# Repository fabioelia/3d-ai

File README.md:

# Caliper

A browser CAD tool for 3D-printable parts, in the spirit of Fusion's sketch → extrude → fillet workflow but with far fewer knobs. Bring the AI you already use (Claude Code, Codex, Cursor, Claude or ChatGPT in the browser) through [AI Connect](https://github.com/fabioelia/ai-connect): it sees, measures and edits the same model you are looking at, while you watch. Caliper calls no model and needs no API key.

**Live:** https://fabioelia.github.io/3d-ai/

- **Real solid modelling.** The geometry kernel is OpenCascade compiled to WebAssembly (through [replicad](https://replicad.xyz)), running in a worker. Fillets, chamfers, shells and booleans are exact B-rep operations, not mesh tricks, and STEP export keeps them exact.
- **Parametric timeline.** Every feature stays editable. Any number can be an expression over named parameters (`width/2 - wall`), and the model rebuilds as you type.
- **Sketching without constraints.** Rectangles, circles, polygons, slots, line paths and text snap to a grid and to each other; exact sizes go in the inspector. A shape drawn inside another becomes a cut-out.
- **Direct manipulation.** Click a face to sketch on it or push/pull it; click edges to fillet or chamfer them; click a face and Shell to hollow the part.
- **Your own AI, through AI Connect.** Your AI gets the whole app as tools: the full state, screenshots of what you see, exact geometry and measurements, printability checks, every edit, your selection, your camera, import and export. See [Use it with your own AI](#use-it-with-your-own-ai-ai-connect).
- **Chat in Caliper.** Type in the side panel; your connected AI listens there, works on the model with the same tools and answers in the panel. Drop, paste or attach images (photos, sketches), 3D files and documents (notes, CSV, schematics such as Eagle `.sch`): text goes with your message, your AI looks at images with the `get_attachments` tool, and 3D files go into the model.
- **3D import.** STL, STEP/STP, OBJ and 3MF, or the zip a model site or a colleague sent. STEP with real surfaces comes in as exact solids; meshes (including Fusion's mesh-only "tessellated" STEP) are repaired automatically (zero-area slivers, T-junctions, duplicate faces, near-miss vertices). Small clean meshes become exact solids whose flat faces you can sketch on, fillet and shell; larger ones become mesh bodies you can move, cut, join and pattern; files that still are not closed solids come in as reference meshes you can view, move, measure and export. Other files in a zip go to the chat when you drop it there.
- **Circuit boards.** Like the board editors in Fusion, Eagle or KiCad. Import an Eagle / Fusion Electronics schematic (`.sch`) or board (`.brd`), or a KiCad board (`.kicad_pcb`), schematic (`.kicad_sch`) or netlist (`.net`): every part comes in with its footprint, pads, body size and height, plus the nets (KiCad schematics and netlists get footprints from KiCad's standard footprint names), and board files also bring their outline, holes, placement and copper. Place parts in a top-down editor (drag, turn with R, flip to the bottom with F, nudge, holes, outline, automatic arrangement on one or both sides) with airwires and live clash checks. Arrange parts automatically with connected parts kept together, or tidy your own layout for shorter connections. Fit the outline to the inside of your enclosure. Route on two copper layers by hand (45° traces, vias) or with the autorouter, add a ground pour (with thermal reliefs for hand soldering), with design-rule checks (clearance, shorts, edge and hole clearance, widths, drills) as you go. Parts are drawn as real-looking 3D models by kind (banded resistors on bent leads, capacitors, headers with pins, modules on their pins, chips), or use your own STEP/STL per part; copper shows in 3D too. Model the enclosure around the board, check the fit, and add printed standoffs with screw pilot holes under the board's mounting holes. Read part heights from a sizes list or BOM text file. Export Gerber and drill files (with a BOM and part positions) for a board house, a BOM on its own, or a `.scr` script that moves the parts in Eagle / Fusion; STL export leaves the electronics out and STEP keeps them.
- **Export.** Binary STL (three mesh qualities) and STEP. Projects save as JSON, with imported STLs embedded, and autosave in the browser.

## Use it with your own AI (AI Connect)

Caliper has no AI of its own. Its tools are registered on the page (WebMCP), and [AI Connect](https://github.com/fabioelia/ai-connect) lets the AI you already use reach them. Every tool call runs against the live model in your tab, so you see each change land in the timeline (and can undo it), and your AI sees what you see. Nothing to install for the first three ways.

Click **Connect AI** in the top bar and pick a way:

| Way | Choose it when | What you do |
|---|---|---|
| **Paste a prompt** | You use Claude Code, Codex, Cursor or another AI that can make web requests. The easiest. | Click **Copy prompt for my AI** and paste it into your AI. It connects itself and starts listening to Caliper's chat panel. Goes through the AI Connect relay, which could read what passes. |
| **Private connection** | Your designs are sensitive. | Click **Open my hub**, **Allow**, then copy the hub's prompt into your AI. End-to-end encrypted: the relay only passes encrypted bytes. Keep the hub window open. |
| **Claude or ChatGPT in the browser** | You chat at claude.ai or chatgpt.com. | Click **Approve Caliper**, **Allow**, and once ever add the connector address it gives you to your chat app. |
| **On this computer only** | Your AI runs on this computer and nothing should leave it. | Once: `claude mcp add ai-connect -- npx -y github:fabioelia/ai-connect mcp` (or that command in any MCP client). Then tell your AI the sentence the menu shows ("Connect to the app with code …"). Chrome or Edge. |

Then type in Caliper's side panel (paste-a-prompt and private routes), or ask your AI in its own window. Changes your AI makes show up beside the model; one chat answer's changes undo together.

What your AI can do: read the document (`get_state`), look (`screenshot`, with labelled faces and edges), measure, query geometry, check printability, replace or edit the model (`set_model`, `edit_model`), select, move the camera, use the interface, show a message, ask you a question in a bar over the model (`ask_user`), import a file it sends as base64 (`import_file`), export (`export_file`: saved in your browser, optionally handed back to the AI), lay out and route boards (`place_parts`, `route_board`, `check_board`), and read the guide. It also gets three skills: the Caliper guide, building an enclosure around a board, and making a part printable.

Security: your AI can do only what Caliper's tools allow, on the page you have open. The prompt works once and expires after 15 minutes; **Disconnect** in the menu revokes the connection. See AI Connect's [security model](https://github.com/fabioelia/ai-connect#security-model).

## Run it

```bash
npm install
npm run dev        # http://127.0.0.1:5173
npm run bundle     # dist/: index.html (single file), kernel.wasm, mesh.wasm, font.ttf
npm run preview    # serve the build on http://127.0.0.1:4173
npm run vendor:ai-connect   # refresh src/vendor/ai-connect.js from an ai-connect checkout at ../ai-connect
```

To try the AI connection against a relay on your own computer, run `npx -y github:fabioelia/ai-connect relay --port 8787` and open Caliper with `?relay=http://127.0.0.1:8787` (only local addresses are accepted there).

## Deploying

The site is served by GitHub Pages from the `gh-pages` branch, which holds only the built files.

```bash
npm run deploy     # build, then replace the gh-pages branch with the new build
```

Each deploy force-pushes one fresh commit to `gh-pages` (nothing but build output lives there). If Pages is not on yet: repository **Settings → Pages → Source: Deploy from a branch → `gh-pages` / root**.

To deploy automatically on every push to `main` instead, copy `deploy/pages.yml` to `.github/workflows/pages.yml` and switch the Pages source to **GitHub Actions**. That workflow installs, runs the kernel tests, builds and publishes; after that `npm run deploy` and the `gh-pages` branch are no longer needed.

The build uses relative URLs, so it works under `/3d-ai/` or any other path without configuration.

`dist/` is a static site; host its four files together anywhere. `index.html` also works opened straight from disk, in which case the kernel and font are fetched from a public CDN instead.

`npm run artifact` additionally writes `dist/artifact.html`, the body-only page for publishing as a Claude artifact. An artifact cannot open AI Connect's connections, so there the chat panel points to the hosted app instead; modelling works as usual, and exports go through the viewer's save prompt (as a `.zip`, because artifacts cannot save `.stl` directly).

## Using it

| To do this | Do this |
| --- | --- |
| Start a part | **Sketch** → pick a plane → drag a rectangle → **Finish sketch** → type the extrude distance. Or add a **Box** / **Cylinder**. Or ask the assistant. |
| Cut a pocket or hole | Click a flat face → **Sketch here** → draw → Finish → set Operation to **Cut** and a negative distance (or Extent: Through all). |
| Push or pull a face | Click a flat face → **Push / pull**. |
| Round or bevel | Click edges (Shift-click for more) → **Fillet** / **Chamfer**. Or click the tool first, then pick. Selecting a face stands for all the edges around it. |
| Hollow out | Click the face to open → **Shell** → wall thickness. |
| Repeat | Select a feature in the timeline → **Pattern** (rows or around an axis) or **Mirror**. |
| Change anything later | Click the feature in the timeline and edit its numbers. Double-click a sketch to reopen it. |
| Drive sizes from one place | Add a parameter (left panel) and type its name into any field. |
| Lay out and route a circuit board | **Board**, or import / drop an Eagle or KiCad file. In the editor drag parts; R turns, F flips to the bottom, Delete removes, arrows nudge, H adds holes; **Auto…** places parts for you. Press X (Route): click a pad, click corners, click the other pad; V drops a via and switches layer. **Auto… → Autoroute** routes the rest. Set the outline, rules and where the board sits in the inspector, pick a part's 3D model (drawn, block, or your STEP), model the enclosure, then **Check fit in enclosure** and **Export Gerbers**. |
| Stack parts of an assembly | Files exported one by one often come in side by side. Select one in the timeline, pick another under **Line up with**, then **Under it**, **On top** or **Centred in it**. |
| Bring in a 3D file | **Import**, File → Import 3D file, or drop files on the window: STL, STEP/STP, OBJ, 3MF, or a zip of them. A zip imports every 3D file in it; several parts keep the layout they share (or are set out in a row if they would overlap). The inspector says how each part came in and what was repaired, and lets you set units, scale, placement and solid or mesh. Drop a zip on the chat instead to also hand its other files (notes, schematics) to Claude. |

Mouse: drag orbits, right-drag pans, scroll zooms. While sketching, drag draws and right-drag orbits. Keys: `S` sketch, `E` extrude, `F` fillet, `Esc` back out, `Ctrl+Z` / `Ctrl+Shift+Z` undo and redo; in a sketch `R` `C` `P` `O` `L` `T` `V` pick the tools.

## How it is put together

| File | Role |
| --- | --- |
| `src/kernel/evaluate.js` | Replays a document (parameters + features) into solids. Pure: runs in the worker and in Node. Caches each step, so editing feature 8 does not rebuild features 1–7. |
| `src/kernel/stl.js` | STL parsing, turning meshes into exact solids or Manifold mesh bodies, and display data for mesh bodies. |
| `src/kernel/worker.js`, `client.js` | The worker that owns OpenCascade and Manifold, and its main-thread handle (latest rebuild wins). |
| `src/files.js` | Imported files: IndexedDB storage and embedding in project files. |
| `src/store.js` | Document, undo/redo, selection, autosave, timeline rollback while sketching or re-picking. |
| `src/viewport.js` | three.js view: bodies, face and edge picking, highlights, camera. |
| `src/sketcher.js`, `sketchgeo.js` | Drawing and editing 2D shapes on a plane. |
| `src/actions.js`, `ui.js`, `schema.js` | Commands, panels, and the per-feature field definitions the inspector is generated from. |
| `src/agent/catalog.js` | The tools: names, descriptions, input schemas. |
| `src/agent/tools.js` | What each tool does inside the page; results are MCP content (text and PNG images). |
| `src/agent/connect.js` | Registers the tools and skills with AI Connect and names who is acting. |
| `src/agent/panel.js` | The Agent menu (AI Connect's ways to connect), your AI's activity in the side panel, confirmations, and the prompt bar for `ask_user`. |
| `src/vendor/ai-connect.js` | The AI Connect web SDK, vendored (`npm run vendor:ai-connect`) because Caliper builds into one self-contained file. |
| `src/assistant.js`, `guide.js` | The side-panel chat (to the AI listening through AI Connect), and the guide every AI gets (the document format and how to work). |
| `src/export.js` | Saving files (direct download, or zipped through the artifact save prompt). |
| `src/board/` | Circuit boards: Eagle reader (`eagle.js`, `xml.js`), KiCad reader (`kicad.js`, `sexpr.js`), footprints from KiCad names (`footprints.js`), placement geometry, checks and auto-arrange (`geometry.js`), copper connectivity, design rules and the autorouter (`route.js`), the 2D editor (`editor.js`), 3D part models and copper (`models.js`, `copper3d.js`), Gerber/drill (`gerber.js`) and Eagle script (`script.js`) export. |

Picked faces and edges are stored with their position in the body *and* a geometric signature. When an earlier dimension changes, the kernel re-finds them and refreshes the signature, so a fillet follows its edge as the part grows. If the edge truly disappears, the feature reports that instead of silently filleting something else.

## Tests

```bash
npm test                 # kernel, 3D import, boards and PCBs (KiCad, routing, DRC, Gerbers): checked against hand-computed values
npm run bundle && node scripts/make-artifact.mjs && npm run preview &
npm run test:e2e         # headless Chromium: modelling flows, import, exports, the board editor, bodies, focus and scroll, AI Connect
```

The end-to-end scripts need Playwright with Chromium available to `require('playwright')`. `scripts/e2e-aiconnect.cjs` starts a local AI Connect relay from an ai-connect checkout (`../ai-connect` after `npm install`, or `AI_CONNECT_DIR`) and plays the person's AI: it follows the pasted prompt, calls Caliper's tools over HTTP, listens to the chat panel and answers there.

## Limits worth knowing

- Sketches have no geometric constraints; shapes are positioned by numbers and snapping.
- A shell fails when the wall is thicker than a fillet or chamfer already on the body. Shell first, fillet after.
- No lofts, sweeps, threads or drafts yet, and no assemblies. Units are millimetres.
- Text uses one font (DejaVu Sans Bold) and shows as a placeholder box until extruded.
- Imported meshes: curved areas of exact-solid imports stay faceted; mesh bodies have no selectable faces or edges, cannot be filleted, chamfered or shelled, and are left out of STEP files. Combining a mesh body with a solid gives a mesh body. Only verifiably closed meshes become solids; anything else (faces folded through each other, internal faces, holes the repair cannot close) is kept as a reference mesh, which never takes part in cuts or joins. Its volume is shown as approximate. IGES is not supported (the bundled OpenCascade build has no IGES reader); STEP assemblies come in as one body per file.
- Boards: two copper layers (inner layers in KiCad files are left out), pours connect through-hole pads with thermal spokes (surface-mount pads solidly) and keep islands, no differential pairs or length tuning. The autorouter is a grid maze router: good for hobby boards, and it reports what it cannot route. Part models are drawn from footprint and size (heights from package descriptions like "29x17.3x4.3", else estimated); KiCad's own `.wrl` models are not read, use the STEP versions. KiCad schematics: one sheet (no hierarchical sub-sheets), footprints from KiCad's standard library names (others become plain blocks). Always check Gerbers in a viewer before ordering.
- The paste-a-prompt route needs an AI that can make web requests, and a chatting AI keeps its session busy while it listens. The on-this-computer route works in Chrome and Edge. Files your AI sends or gets back pass through the relay, which caps a message at about 1 MB.

OpenCascade is LGPL-2.1; replicad, three.js and AI Connect are MIT; Manifold is Apache-2.0; DejaVu fonts are under the Bitstream Vera licence.

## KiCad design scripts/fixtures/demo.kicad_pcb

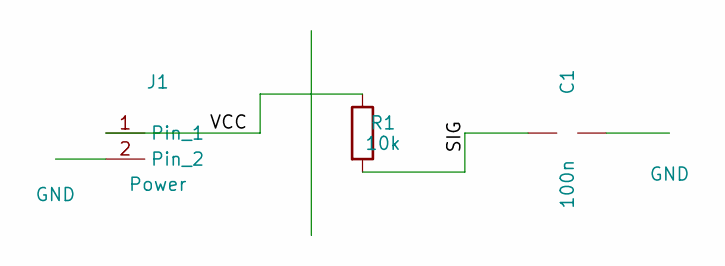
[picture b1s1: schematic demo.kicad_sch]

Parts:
C1: 100n; C_0805_2012Metric
J1: Power; PinHeader_1x02_P2.54mm_Vertical
R1: 10k; R_Axial_DIN0207_L6.3mm_D2.5mm_P10.16mm_Horizontal

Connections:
GND: C1.2, J1.2
SIG: C1.1, R1.2
VCC: J1.1, R1.1

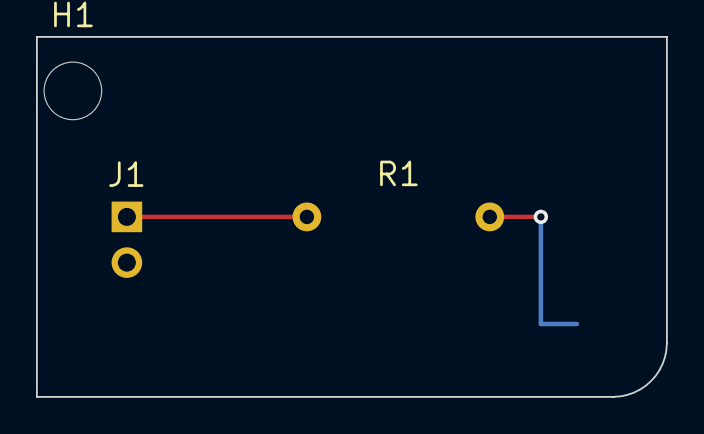
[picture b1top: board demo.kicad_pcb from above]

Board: 2 copper layers, 35.0 x 20.0 mm, 4 parts (1 on the bottom side), 3 nets.

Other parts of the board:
H1: MountingHole_3.2mm_M3
